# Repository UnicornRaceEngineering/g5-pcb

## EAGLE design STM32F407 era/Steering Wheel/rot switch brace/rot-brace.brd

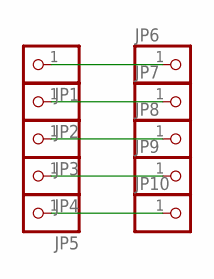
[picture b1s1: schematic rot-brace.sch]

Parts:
JP1, JP2, JP3, JP4, JP5, JP6, JP7, JP8, JP9, JP10: HEADER-1X1ROUND; 1X01_ROUND

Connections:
unnamed: JP5.1, JP10.1
unnamed: JP4.1, JP9.1
unnamed: JP3.1, JP8.1
unnamed: JP2.1, JP7.1
unnamed: JP1.1, JP6.1

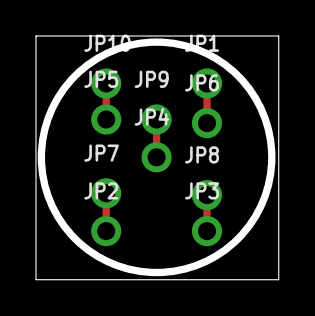
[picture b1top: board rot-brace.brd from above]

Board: 2 copper layers, 13.5 x 13.5 mm, 10 parts (0 on the bottom side), 5 nets.

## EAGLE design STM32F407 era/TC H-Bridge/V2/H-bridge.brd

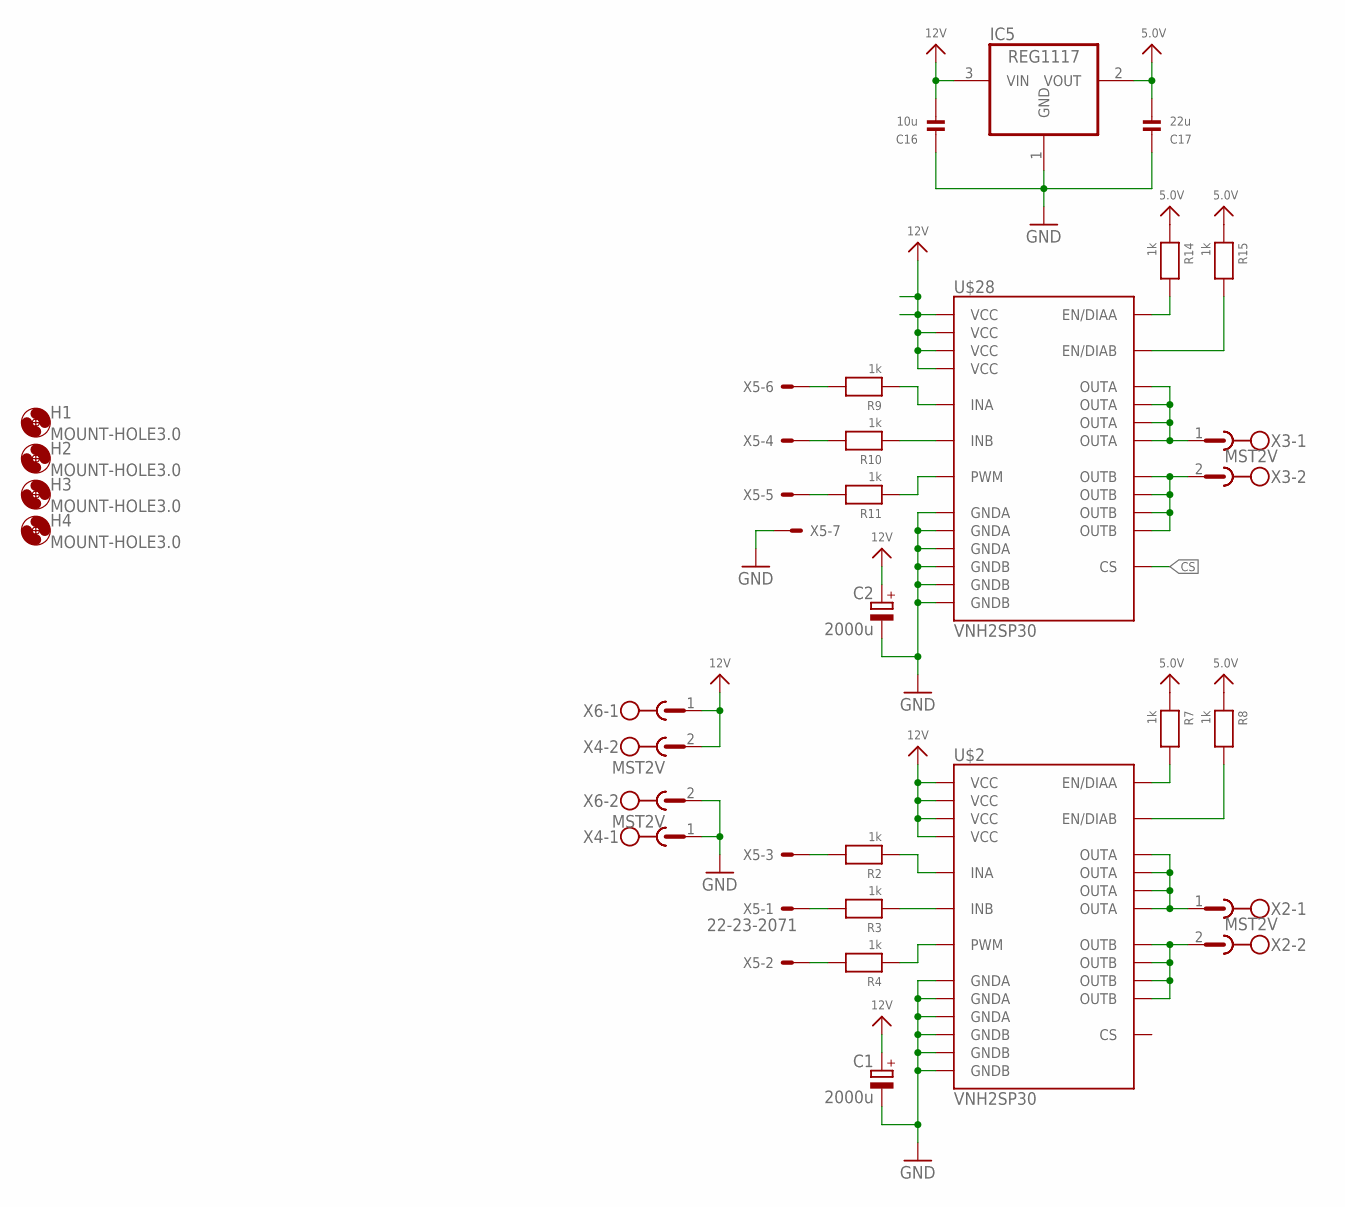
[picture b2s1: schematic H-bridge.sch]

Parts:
C1, C2: 2000u; EB22,5D
C16: 10u; _0805
C17: 22u; _0805
H1, H2, H3, H4: MOUNT-HOLE3.0; 3,0
IC5: REG1117; SOT223
R2, R3, R4, R7, R8, R9, R10, R11, R14, R15: 1k; _0603
U$2, U$28: VNH2SP30
X2, X3, X4, X6: MST2V; MSTBV2
X5: 22-23-2071

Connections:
5.0V: C17.2, IC5.2 (VOUT), R7.1, R8.1, R14.1, R15.1
12V: C1.+, C2.+, C16.2, IC5.3 (VIN), U$2.3 (VCC), U$2.13 (VCC), U$2.23 (VCC), U$2.SLUG1 (VCC), U$28.3 (VCC), U$28.13 (VCC), U$28.23 (VCC), U$28.SLUG1 (VCC), X4.2, X6.1
CS: U$28.9 (CS)
CVVM: U$28.15 (OUTB), U$28.16 (OUTB), U$28.21 (OUTB), U$28.SLUG2 (OUTB), X3.2
EN1H: R14.2, U$28.6 (EN/DIAA)
EN2H: R15.2, U$28.10 (EN/DIAB)
GND: C1.-, C2.-, C16.1, C17.1, IC5.1 (GND), U$2.18 (GNDB), U$2.19 (GNDB), U$2.20 (GNDB), U$2.26 (GNDA), U$2.27 (GNDA), U$2.28 (GNDA), U$28.18 (GNDB), U$28.19 (GNDB), U$28.20 (GNDB), U$28.26 (GNDA), U$28.27 (GNDA), U$28.28 (GNDA), X4.1, X5.7, X6.2
unnamed: R3.2, X5.1
unnamed: R4.2, X5.2
unnamed: R7.2, U$2.6 (EN/DIAA)
unnamed: R8.2, U$2.10 (EN/DIAB)
unnamed: R2.1, U$2.5 (INA)
unnamed: R3.1, U$2.11 (INB)
unnamed: R4.1, U$2.8 (PWM)
unnamed: R2.2, X5.3
unnamed: R10.2, X5.4
unnamed: U$2.1 (OUTA), U$2.25 (OUTA), U$2.30 (OUTA), U$2.SLUG3 (OUTA), X2.1
unnamed: U$2.15 (OUTB), U$2.16 (OUTB), U$2.21 (OUTB), U$2.SLUG2 (OUTB), X2.2
unnamed: R11.2, X5.5
unnamed: R9.2, X5.6
unnamed: R11.1, U$28.8 (PWM)
unnamed: R10.1, U$28.11 (INB)
unnamed: R9.1, U$28.5 (INA)
OUTA: U$28.1 (OUTA), U$28.25 (OUTA), U$28.30 (OUTA), U$28.SLUG3 (OUTA), X3.1

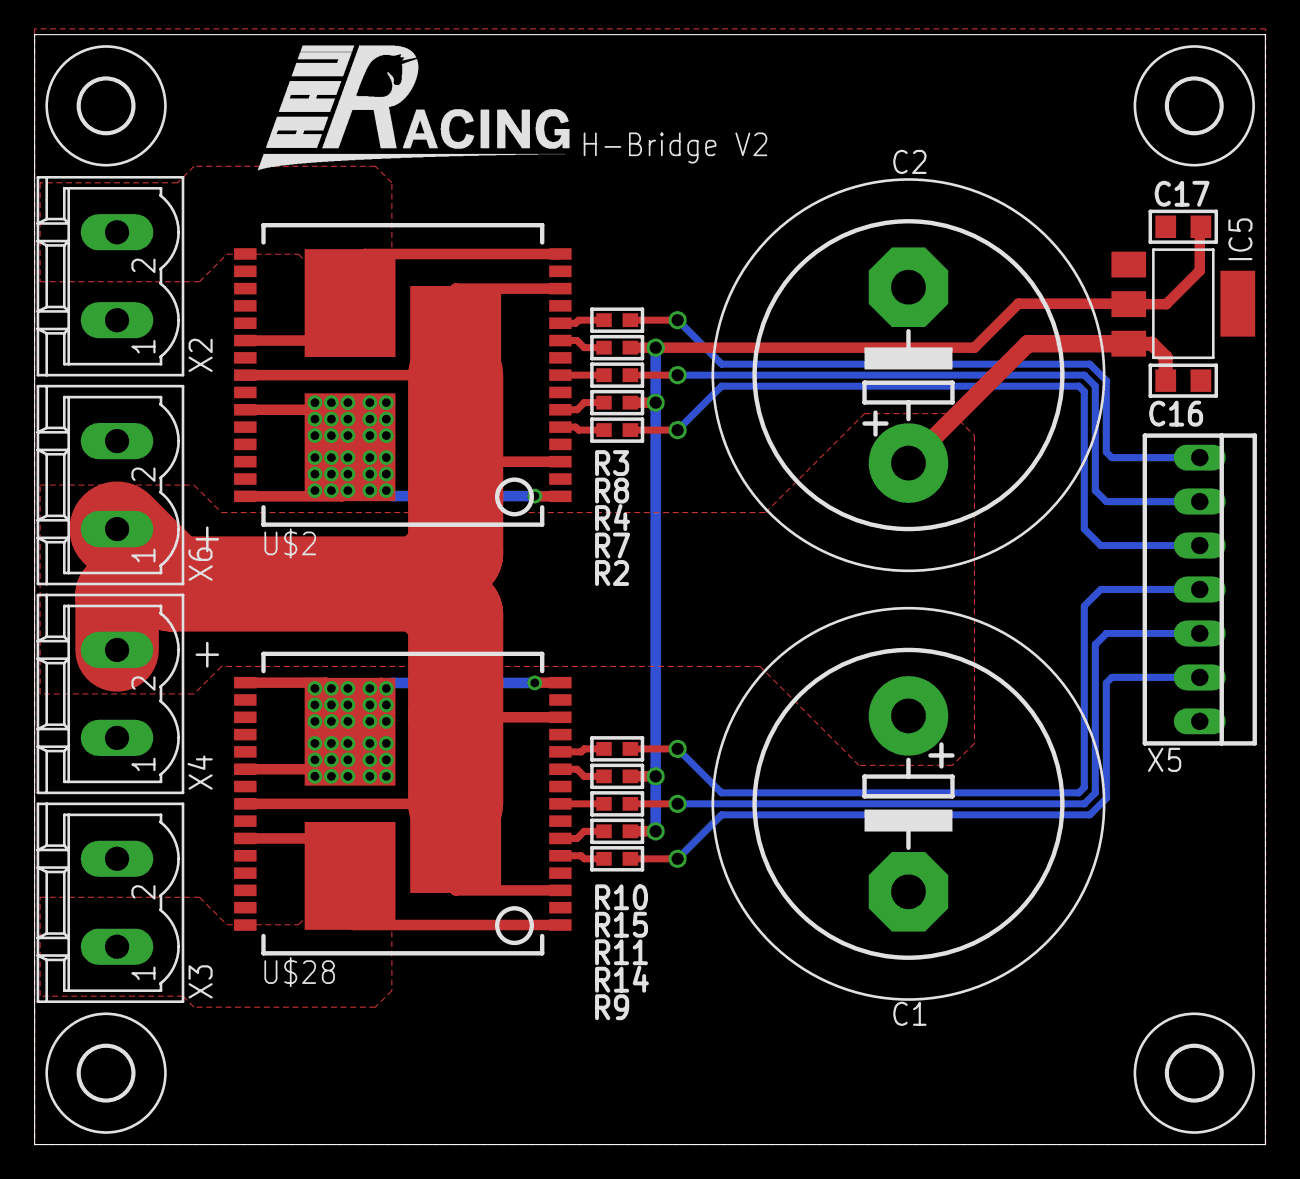
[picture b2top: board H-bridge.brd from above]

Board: 2 copper layers, 71.1 x 64.1 mm, 26 parts (0 on the bottom side), 23 nets.

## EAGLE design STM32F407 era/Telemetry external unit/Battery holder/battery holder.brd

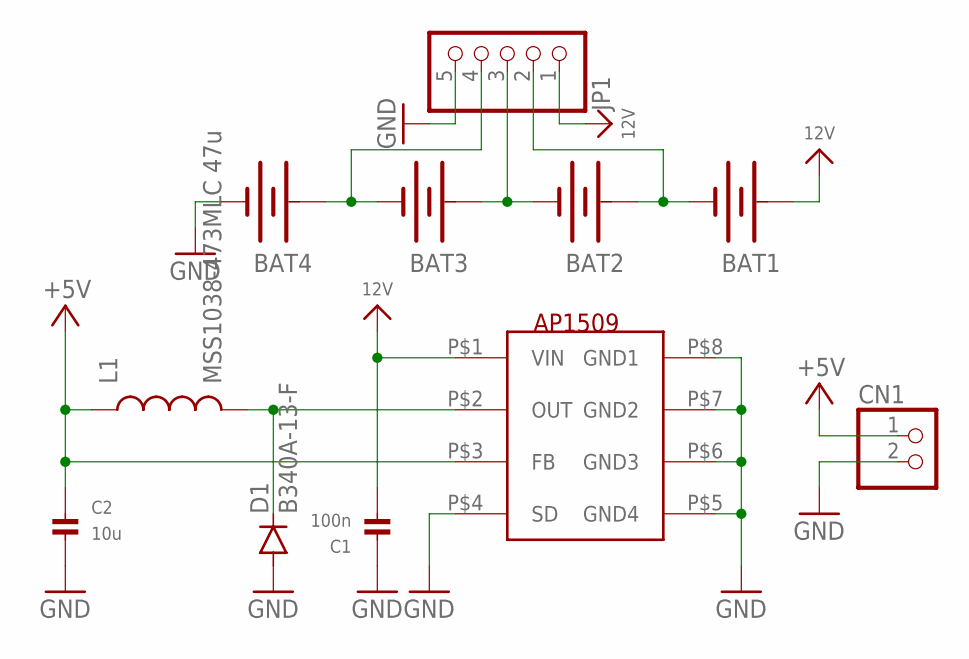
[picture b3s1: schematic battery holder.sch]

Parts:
BAT1, BAT2, BAT3, BAT4: BATTERY18650; BATTERY_18650-HOLDER
C1: 100n; _0603MP
C2: 10u; _0805MP
CN1: JST_2PIN; JSTPH2
D1: B340A-13-F; SMA-DIODE
JP1: PINHD-1X5/90; 1X05/90
L1: MSS1038-473MLC 47u; CDRH125
U$3: AP1509; SOP-8L

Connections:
12V: BAT1.PWR@1 (+), C1.2, JP1.1, U$3.P$1 (VIN)
+5V: C2.1, CN1.1, L1.1, U$3.P$3 (FB)
GND: BAT4.GND@1 (-), C1.1, C2.2, CN1.2, D1.A, JP1.5, U$3.P$4 (SD), U$3.P$5 (GND4), U$3.P$6 (GND3), U$3.P$7 (GND2), U$3.P$8 (GND1)
unnamed: BAT1.GND@1 (-), BAT2.PWR@1 (+), JP1.2
unnamed: BAT2.GND@1 (-), BAT3.PWR@1 (+), JP1.3
unnamed: BAT3.GND@1 (-), BAT4.PWR@1 (+), JP1.4
unnamed: D1.C, L1.2, U$3.P$2 (OUT)

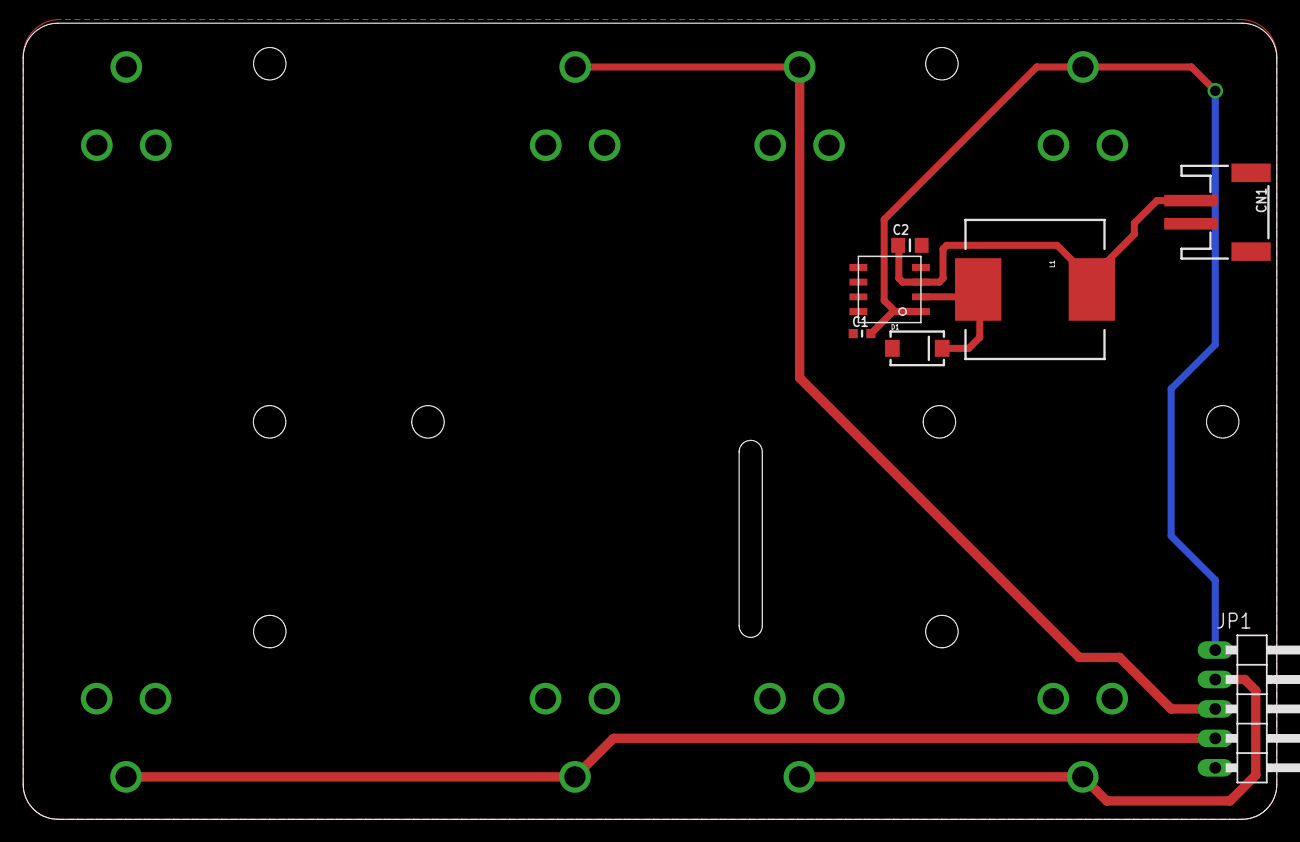
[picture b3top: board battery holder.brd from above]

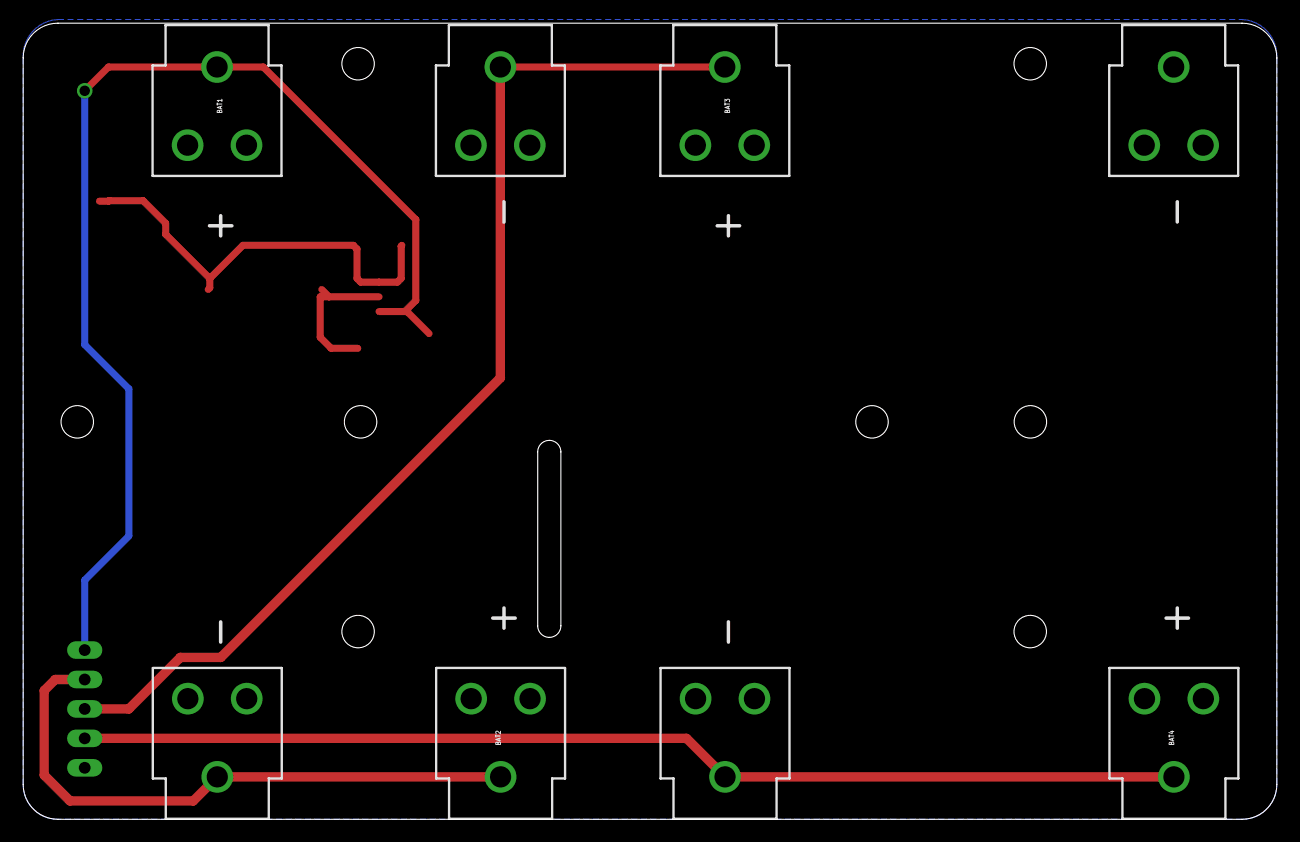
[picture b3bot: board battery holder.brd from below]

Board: 2 copper layers, 108.2 x 68.7 mm, 11 parts (4 on the bottom side), 7 nets.

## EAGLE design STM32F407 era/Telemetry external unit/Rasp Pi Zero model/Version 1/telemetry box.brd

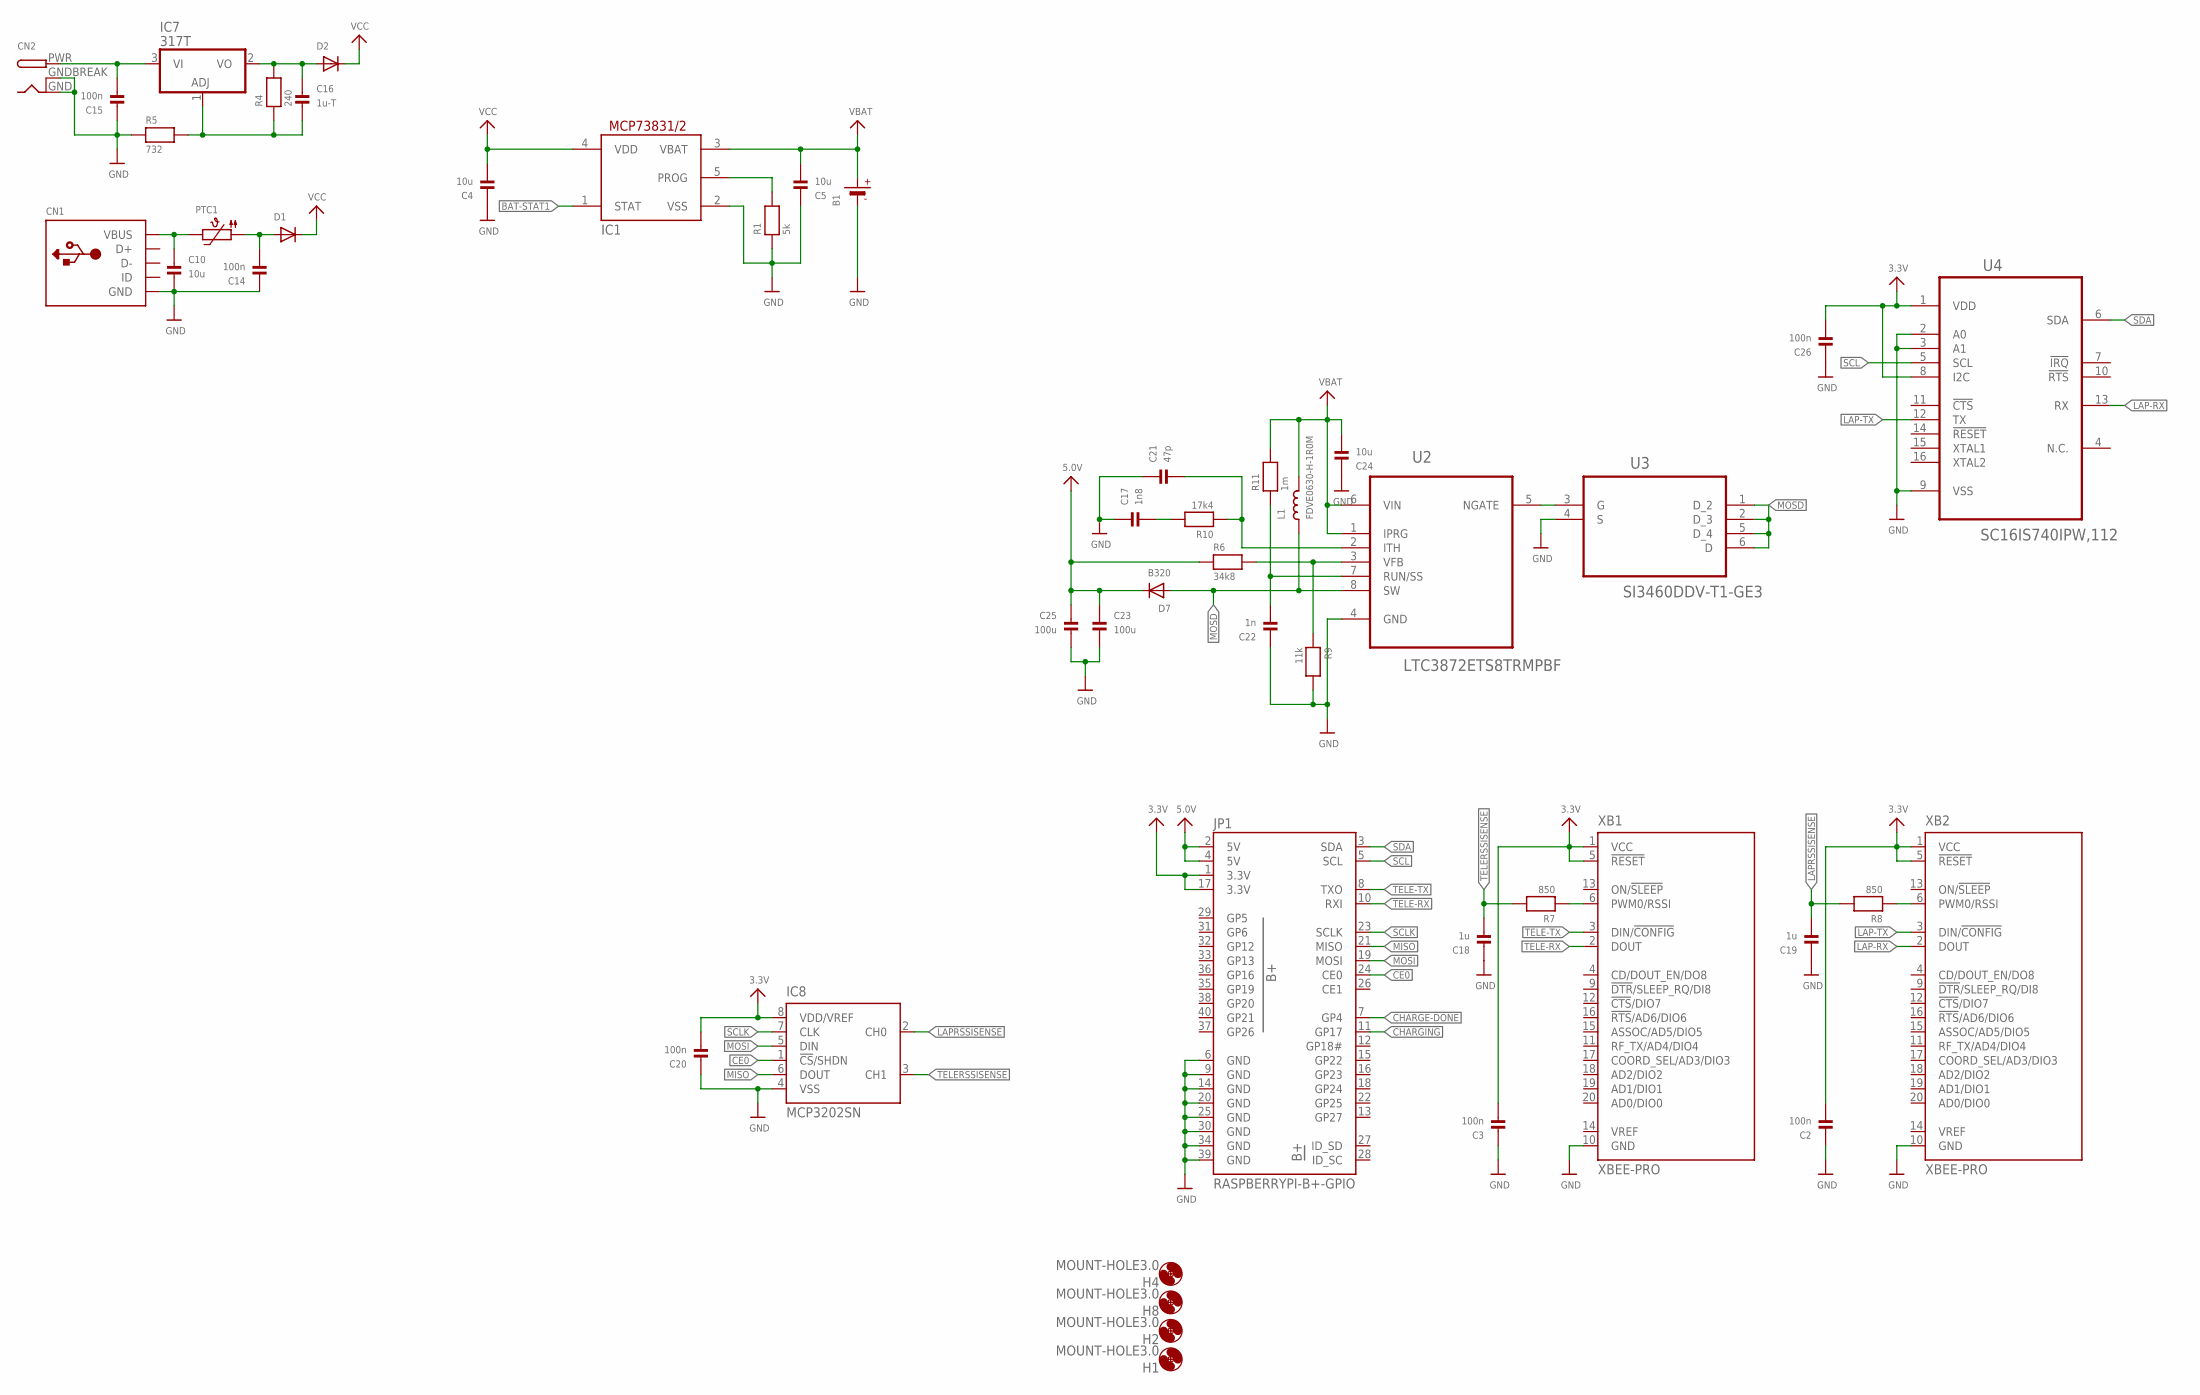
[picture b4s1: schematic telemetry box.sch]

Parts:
B1: BATTERY; JSTPH2
C2, C3, C14, C15, C20, C26: 100n; _0603
C4, C5, C10, C24: 10u; _0805
C16: 1u-T; _0603
C17: 1n8; _0603
C18, C19: 1u; _0603
C21: 47p; _0603
C22: 1n; _0603
C23, C25: 100u; 1206
CN1: USBMINIB; USB-MINIB
CN2: DCBARRELPTH; DCJACK_2MM_PTH
D1, D2: DIODESOT23_WAVE; SOT23-W
D7: B320; SMADIODE
H1, H2, H4, H8: MOUNT-HOLE3.0; 3,0
IC1: MCP73831/OT; SOT23-5L
IC7: 317T; TO220H
IC8: MCP3202SN; SO-08
JP1: RASPBERRYPI-B+-GPIO; 2X20-SHROUDED
L1: FDVE0630-H-1R0M; INDUCTOR_6X6MM_TDK_SLF6045
PTC1: PTC1206; 1206
R1: 5k; _0603
R4: 240; _0603
R5: 732; _0603
R6: 34k8; _0603
R7, R8: 850; _0603
R9: 11k; _0603
R10: 17k4; _0603
R11: 1m; _0603
U2: LTC3872ETS8TRMPBF; SOT65P280X100-8N
U3: SI3460DDV-T1-GE3; SOT95P285X110-6N
U4: SC16IS740IPW,112; SOP65P640X110-16N
XB1, XB2: XBEE-PRO

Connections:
3.3V: C2.2, C3.2, C20.2, C26.2, IC8.8 (VDD/VREF), JP1.1 (3.3V), JP1.17 (3.3V), U4.1 (VDD), U4.8 (I2C), XB1.1 (VCC), XB1.5 (!RESET), XB2.1 (VCC), XB2.5 (!RESET)
5.0V: C23.1, C25.1, D7.C, JP1.2 (5V), JP1.4 (5V), R6.1
BAT-STAT1: IC1.1 (STAT)
CE0: IC8.1 (!CS!/SHDN), JP1.24 (CE0)
CHARGE-DONE: JP1.7 (GP4)
CHARGING: JP1.11 (GP17)
GND: B1.1 (-), C2.1, C3.1, C4.1, C5.1, C10.2, C14.1, C15.1, C17.1, C18.1, C19.1, C20.1, C21.1, C22.1, C23.2, C24.1, C25.2, C26.1, CN1.GND, CN2.GND, CN2.GNDBREAK, IC1.2 (VSS), IC8.4 (VSS), JP1.6 (GND), JP1.9 (GND), JP1.14 (GND), JP1.20 (GND), JP1.25 (GND), JP1.30 (GND), JP1.34 (GND), JP1.39 (GND), R1.1, R5.1, R9.2, U2.4 (GND), U3.4 (S), U4.2 (A0), U4.3 (A1), U4.9 (VSS), XB1.10 (GND), XB2.10 (GND)
LAP-RX: U4.13 (RX), XB2.2 (DOUT)
LAP-TX: U4.12 (TX), XB2.3 (DIN/!CONFIG)
LAPRSSISENSE: C19.2, IC8.2 (CH0), R8.2
MISO: IC8.6 (DOUT), JP1.21 (MISO)
MOSD: D7.A, L1.P$1 (1), U2.8 (SW), U3.1 (D_2), U3.2 (D_3), U3.5 (D_4), U3.6 (D)
MOSI: IC8.5 (DIN), JP1.19 (MOSI)
unnamed: IC1.5 (PROG), R1.2
unnamed: C10.1, CN1.VBUS, PTC1.2
unnamed: C16.2, IC7.1 (ADJ), R4.1, R5.2
unnamed: R6.2, R9.1, U2.3 (VFB)
unnamed: C16.1, D2.1 (A), IC7.2 (VO), R4.2
unnamed: C14.2, D1.1 (A), PTC1.1
unnamed: C15.2, CN2.PWR, IC7.3 (VI)
unnamed: R7.1, XB1.6 (PWM0/RSSI)
unnamed: R8.1, XB2.6 (PWM0/RSSI)
unnamed: U2.5 (NGATE), U3.3 (G)
unnamed: C17.2, R10.2
unnamed: C21.2, R10.1, U2.2 (ITH)
unnamed: C22.2, R11.1, U2.7 (RUN/SS)
SCL: JP1.5 (SCL), U4.5 (SCL)
SCLK: IC8.7 (CLK), JP1.23 (SCLK)
SDA: JP1.3 (SDA), U4.6 (SDA)
TELE-RX: JP1.10 (RXI), XB1.2 (DOUT)
TELE-TX: JP1.8 (TXO), XB1.3 (DIN/!CONFIG)
TELERSSISENSE: C18.2, IC8.3 (CH1), R7.2
VBAT: B1.2 (+), C5.2, C24.2, IC1.3 (VBAT), L1.P$2 (2), R11.2, U2.1 (IPRG), U2.6 (VIN)
VCC: C4.2, D1.3 (C), D2.3 (C), IC1.4 (VDD)

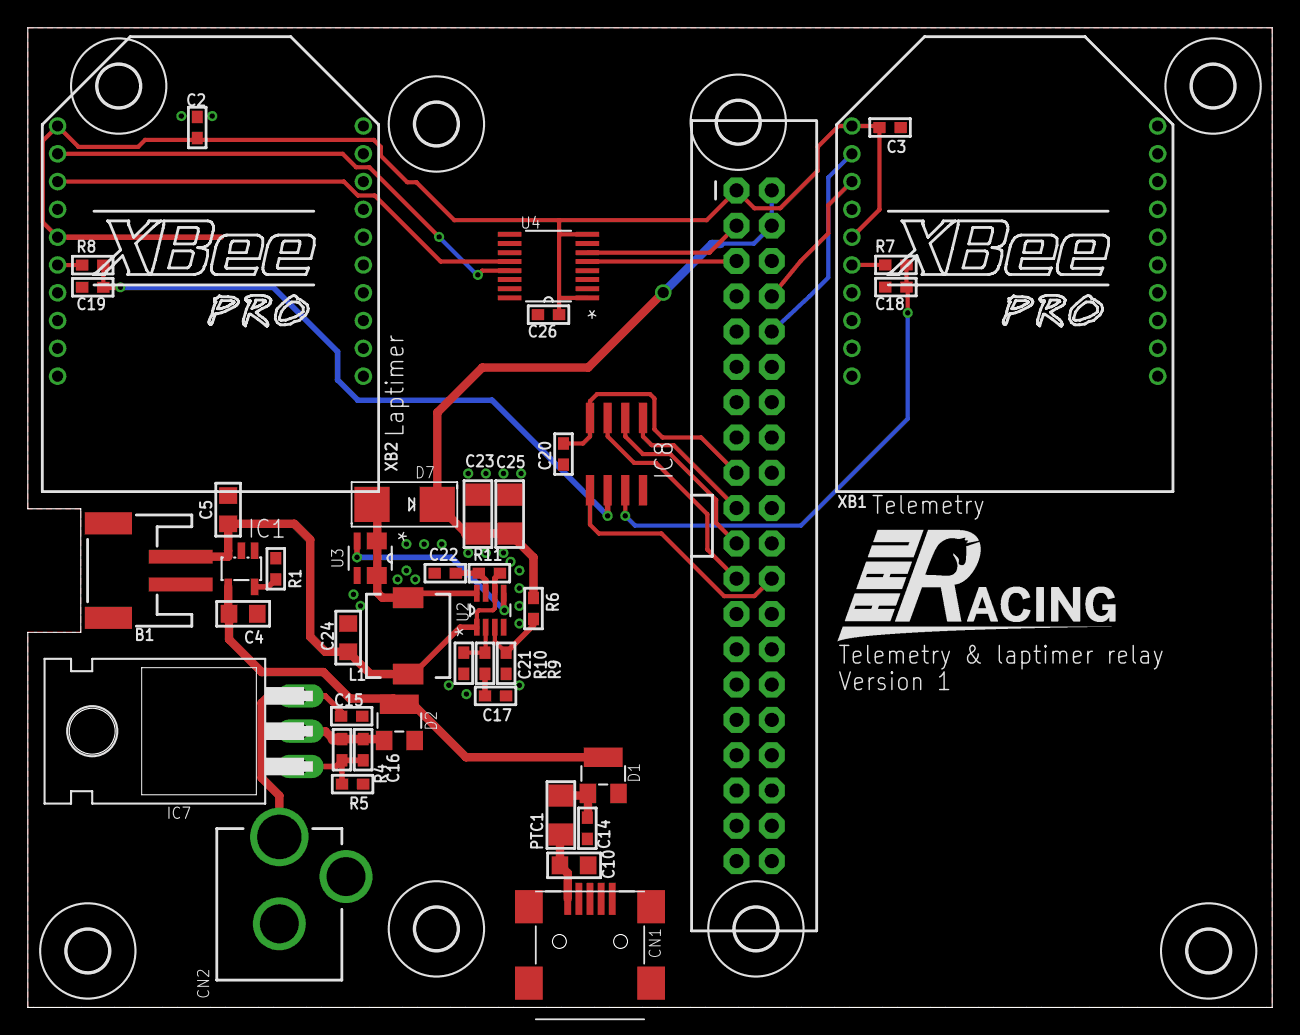
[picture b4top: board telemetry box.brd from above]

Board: 2 copper layers, 89.5 x 70.5 mm, 52 parts (0 on the bottom side), 31 nets.

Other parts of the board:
H3, H5, H6, H7: MOUNT-HOLE3.0; 3,0

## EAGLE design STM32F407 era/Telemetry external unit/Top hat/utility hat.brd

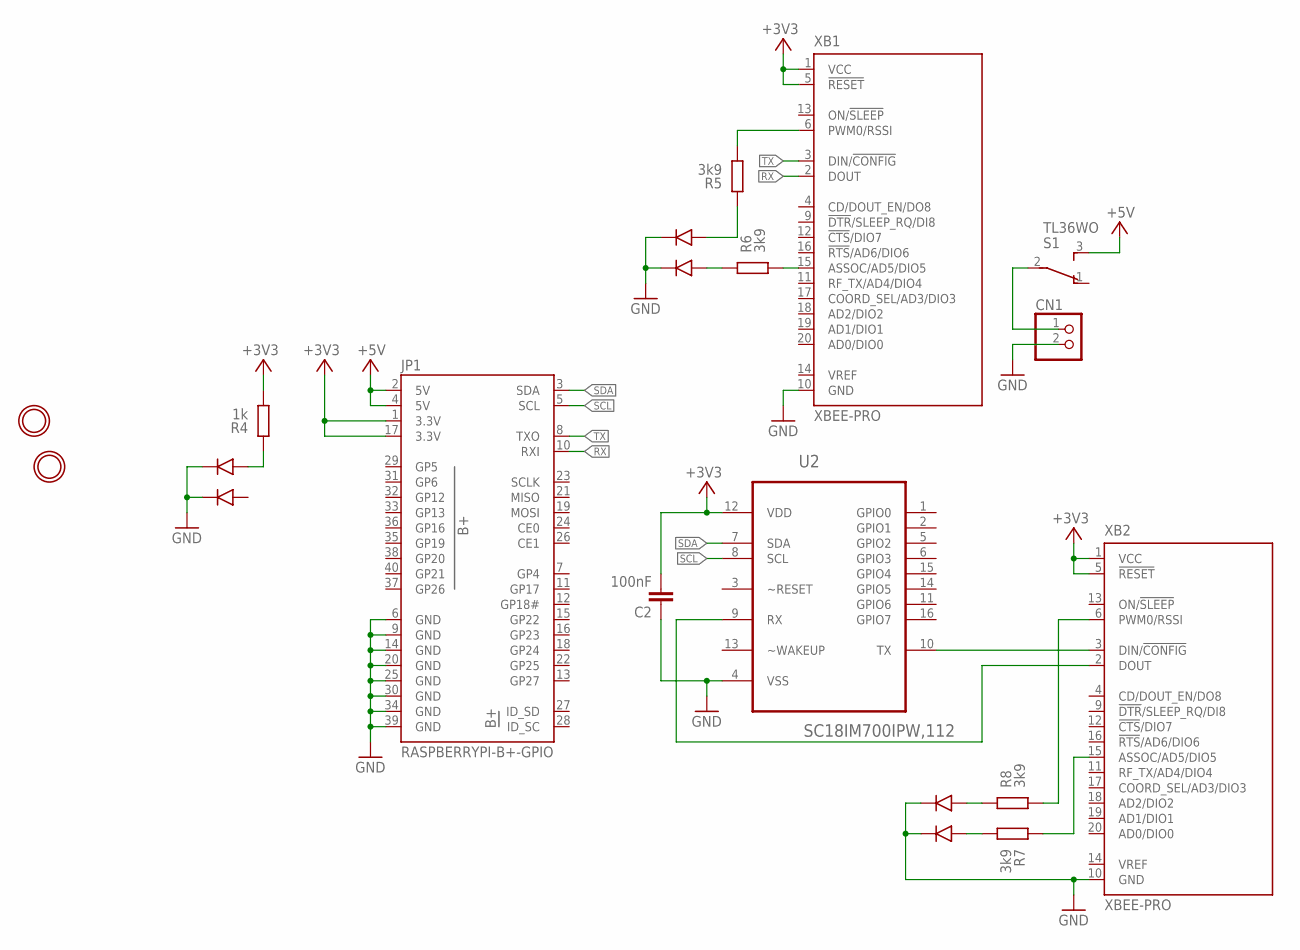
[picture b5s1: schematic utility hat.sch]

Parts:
C2: 100nF; C0805K
CN1: JST_2PIN; JSTPH2
JP1: RASPBERRYPI-B+-GPIO; 2X20-SHROUDED
R4: 1k; M0805; TOLERANCE 5%
R5, R6, R7, R8: 3k9; M0805; TOLERANCE 5%
S1: TL36WO; TL3XWO
U2: SC18IM700IPW,112; SOP65P640X110-16N
U$1, U$2, U$3: BI-LEVEL-LED-INDICATOR
U$4, U$5: MOUNTINGHOLE3.0THIN; MOUNTINGHOLE_3.0_PLATEDTHIN
XB1: XBEE-PRO
XB2: XBEE-PRO; MPN XBP24-AWI-001

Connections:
+3V3: C2.2, JP1.1 (3.3V), JP1.17 (3.3V), R4.1, U2.12 (VDD), XB1.1 (VCC), XB1.5 (!RESET), XB2.1 (VCC), XB2.5 (!RESET)
+5V: JP1.2 (5V), JP1.4 (5V), S1.3 (S)
GND: C2.1, CN1.2, JP1.6 (GND), JP1.9 (GND), JP1.14 (GND), JP1.20 (GND), JP1.25 (GND), JP1.30 (GND), JP1.34 (GND), JP1.39 (GND), U2.4 (VSS), U$1.CATHODE1, U$1.CATHODE2, U$2.CATHODE1, U$2.CATHODE2, U$3.CATHODE1, U$3.CATHODE2, XB1.10 (GND), XB2.10 (GND)
unnamed: U2.10 (TX), XB2.3 (DIN/!CONFIG)
unnamed: U2.9 (RX), XB2.2 (DOUT)
unnamed: R4.2, U$3.ANODE1
unnamed: R6.1, XB1.15 (ASSOC/AD5/DIO5)
unnamed: R6.2, U$1.ANODE2
unnamed: R5.1, XB1.6 (PWM0/RSSI)
unnamed: R5.2, U$1.ANODE1
unnamed: R7.1, U$2.ANODE2
unnamed: R8.2, U$2.ANODE1
unnamed: R7.2, XB2.15 (ASSOC/AD5/DIO5)
unnamed: R8.1, XB2.6 (PWM0/RSSI)
unnamed: CN1.1, S1.2
RX: JP1.10 (RXI), XB1.2 (DOUT)
SCL: JP1.5 (SCL), U2.8 (SCL)
SDA: JP1.3 (SDA), U2.7 (SDA)
TX: JP1.8 (TXO), XB1.3 (DIN/!CONFIG)

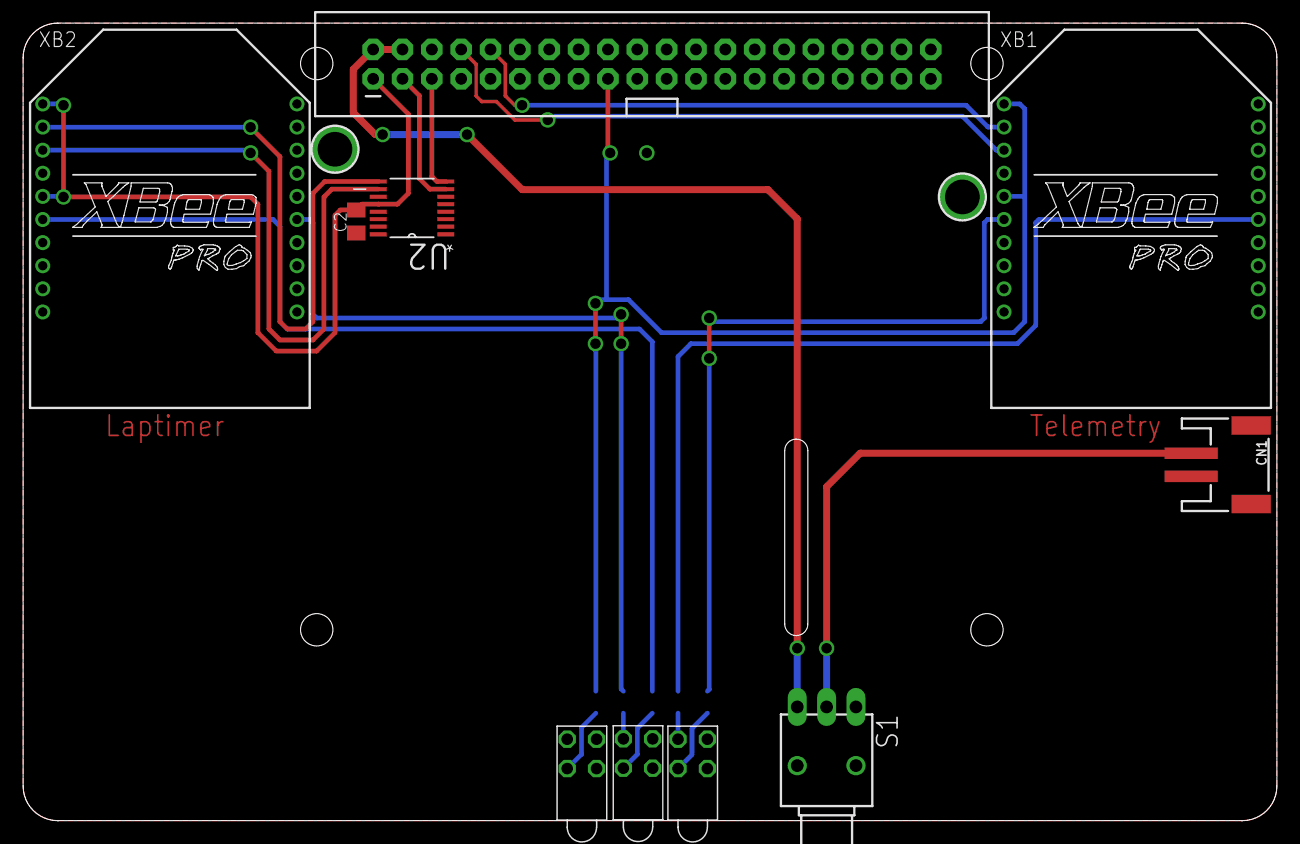
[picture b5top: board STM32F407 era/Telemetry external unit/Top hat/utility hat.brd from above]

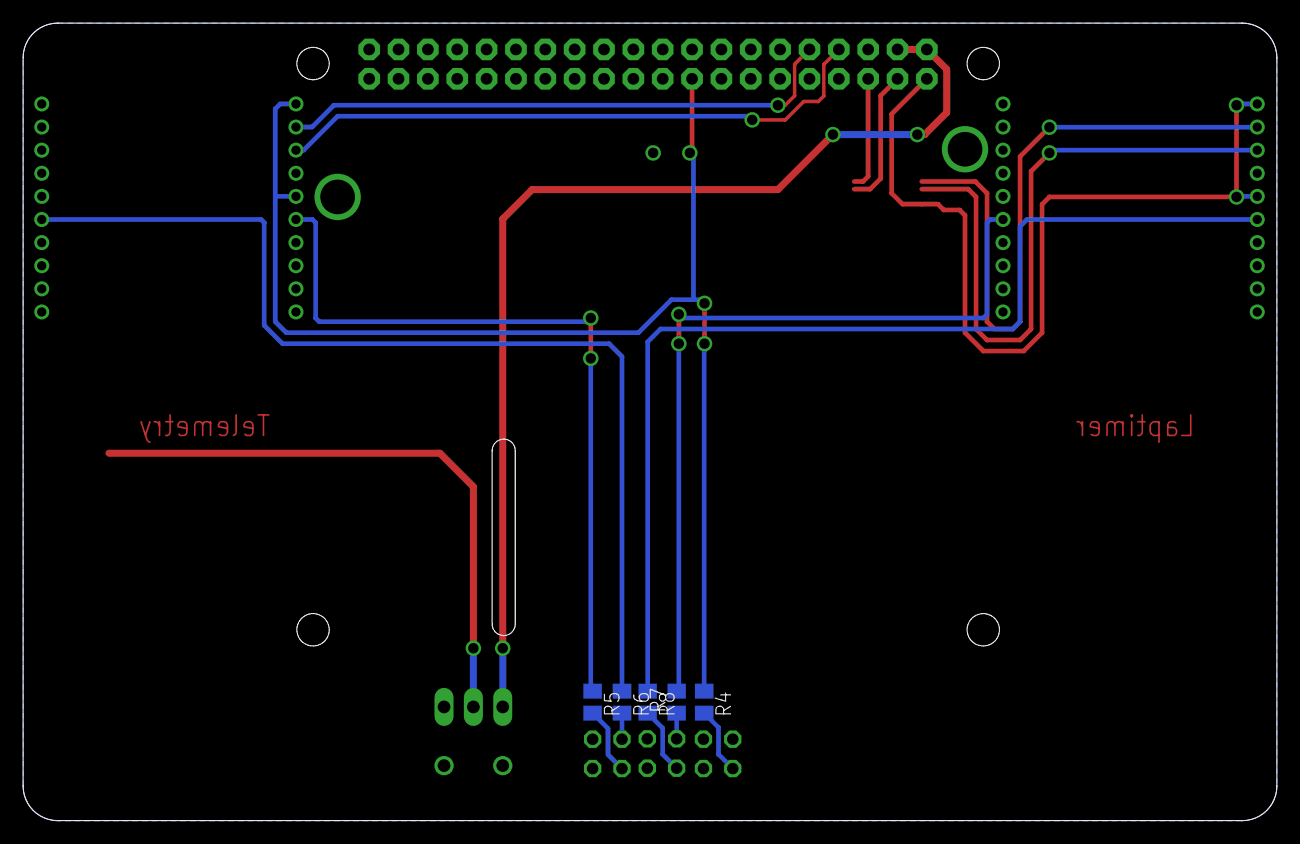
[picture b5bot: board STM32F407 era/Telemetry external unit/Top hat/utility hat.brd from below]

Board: 2 copper layers, 108.5 x 69.0 mm, 17 parts (5 on the bottom side), 19 nets.

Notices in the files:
parts and their libraries:
microbuilder: This work is placed in the public domain, and may be freely used for commercial and non-commercial work with the following conditions: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
SparkFun-PowerIC: Licensing: Creative Commons ShareAlike 4.0 International - https://creativecommons.org/licenses/by-sa/4.0
